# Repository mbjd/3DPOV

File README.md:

# 3DPOV

This is the github repo for my 3D persistence of vision display. Here you
can find the arduino/teensy source code (`./code/`), eagle schematic and
board files (`./Eagle/`), and the python program I wrote to simplify the
creation of images containing simple shapes (`./image_creation/`).

### Videos

[one](https://www.youtube.com/watch?v=bCETWNgBxbI) [two](https://www.youtube.com/watch?v=-gFsKhf5J-I)

### Summary

This was my Matura project (the end of (the equivalent of) high school in
Switzerland), and I did most of the work in the second half of 2014. You
can find various more detailed reports below, but here's a quick summary:

The *very* basic idea is this: We have a 2D display
and rotate it quickly through the third dimension. By controlling each 
pixel in a precisely timed way, we can light up a set of points in 3D 
space, but only at specific times (when the corresponding pixel is
physically at the right spot). When this rotation is fast enough, 
[persistence of vision](https://en.wikipedia.org/wiki/Persistence_of_vision) 
will make it seem like an actual 3D image is continuously displayed. 

The display itself consists of 10 LED rows mounted in a double-helix
arrangement. Each of them contains 16 RGB LEDs driven by three shift
registers, for a total of 480 LEDs or 160 Pixels.

The shift registers are controlled by a Teensy 3.1 microcontroller board
using an SPI bus (All 30 shift registers are daisy chained together). The
controller is mounted on a wooden disc below the ten LED boards.

All of this is mounted on a 4mm steel shaft, supplied with 3.3V DC using
two copper slip rings, and spun up to 60 Hz by a brushed DC motor. A hall
sensor and a magnet enable the controller to measure the rotational speed
and to adjust its timing, so that the image always stays still despite the
speed not being quite constant. The image is updated 100 times per
revolution, or 6000 times a second.

Currently there's no way to supply images at runtime, the display has to be
stopped so that a new program can be uploaded using the Teensy's USB port.

### Various versions of the paper

[Original in German](https://drive.google.com/file/d/0B2iq6C3wqe05aEx5dVFoNF9xR28/view?usp=sharing&resourcekey=0-dw7vPy6Eh3UUGyYrgM35uw)

[English long version, not quite finished](https://github.com/mbjd/english-paper/blob/master/paper.pdf)

[English short version](https://github.com/mbjd/english-paper/blob/master/paper-short.pdf)

[Other english stuff](https://github.com/mbjd/english-paper)

### Press etc

[Hackaday article](http://hackaday.com/2016/11/16/spinning-3d-pov-display-as-a-high-school-term-project/)

[ETHZ D-ITET in German](https://www.ee.ethz.ch/de/news-und-veranstaltungen/d-itet-news-channel/2016/09/d-itet-student-gewinnt-forschungs-preis-.html) or [English](https://www.ee.ethz.ch/news-and-events/d-itet-news-channel/2016/09/d-itet-student-wins-research-award.html)

[Swiss Youth in Science article](http://web.archive.org/web/20161117130814/http://sjf.ch/eucys-2016-eth-student-gewinnt-forschungs-preis-am-ersten-studientag/)

[EUCYS 2016 link](http://eucys2016.eu/development-of-a-3d-display/)

### Links to discussion

[one](http://www.reddit.com/r/electronics/comments/2m6apx/finally_my_led_board_works_had_to_make_a_little/) [two](http://www.reddit.com/r/electronics/comments/2nrek4/almost_working_3d_pov_display/) [three](http://www.reddit.com/r/electronics/comments/2q9sg6/my_3d_pov_in_action_as_promised/)

### Photos

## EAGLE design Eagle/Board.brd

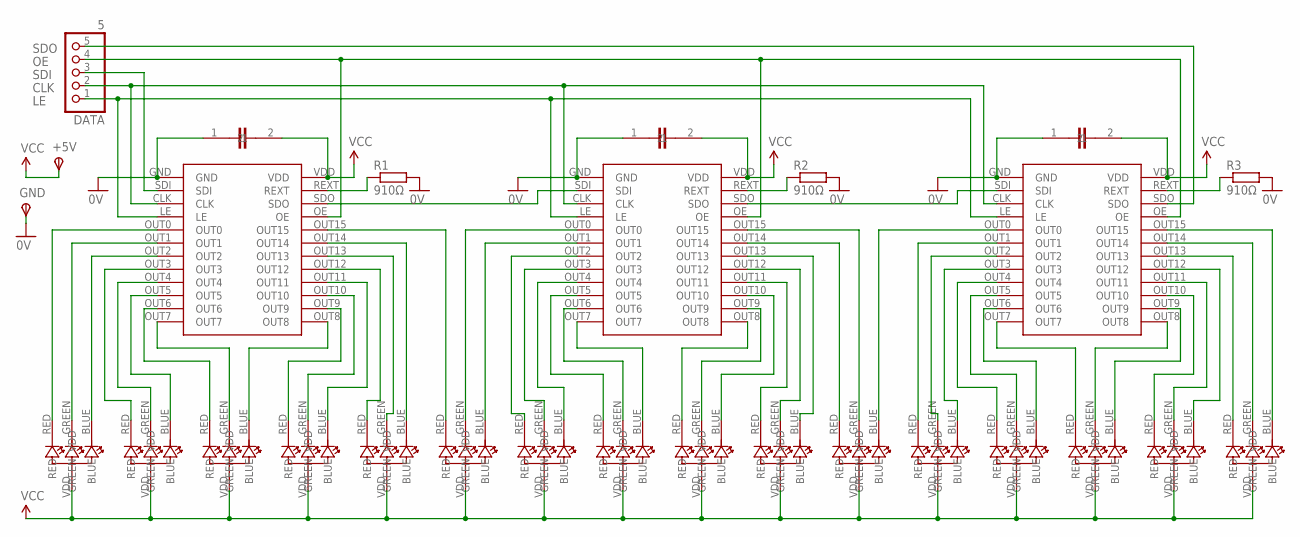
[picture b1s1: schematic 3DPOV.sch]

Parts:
+5V: TPSPAD1-20; P1-20
CAP1, CAP2, CAP3: 1µF; CAP
DATA: 5; 1X05
GND: TPSPAD1-20; P1-20
IC1, IC2, IC3: TLC5927; DBQ
R1, R2, R3: 910Ω; 0207/7
U$1, U$2, U$4, U$5, U$6, U$7, U$10, U$11, U$12, U$13, U$14, U$15, U$16, U$17, U$18, U$19: SMDLED

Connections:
0V: CAP1.1, CAP2.1, CAP3.1, GND.TP, IC1.GND, IC2.GND, IC3.GND, R1.2, R2.2, R3.2
CLK: DATA.2, IC1.CLK, IC2.CLK, IC3.CLK
LE: DATA.1, IC1.LE, IC2.LE, IC3.LE
unnamed: IC1.OUT0, U$4.RED
unnamed: IC1.OUT1, U$4.GREEN
unnamed: IC1.OUT2, U$4.BLUE
unnamed: IC1.OUT3, U$5.RED
unnamed: IC1.OUT4, U$5.GREEN
unnamed: IC1.OUT5, U$5.BLUE
unnamed: IC1.OUT7, U$6.GREEN
unnamed: IC1.OUT6, U$6.RED
unnamed: IC1.OUT8, U$6.BLUE
unnamed: IC1.OUT9, U$7.RED
unnamed: IC1.OUT10, U$7.GREEN
unnamed: IC1.OUT11, U$7.BLUE
unnamed: IC1.OUT12, U$2.RED
unnamed: IC1.OUT13, U$2.GREEN
unnamed: IC1.OUT14, U$2.BLUE
unnamed: IC1.OUT15, U$1.RED
unnamed: IC2.OUT0, U$1.GREEN
unnamed: IC2.OUT1, U$1.BLUE
unnamed: IC2.OUT2, U$10.RED
unnamed: IC2.OUT3, U$10.GREEN
unnamed: IC2.OUT4, U$10.BLUE
unnamed: IC2.OUT7, U$11.BLUE
unnamed: IC2.OUT6, U$11.GREEN
unnamed: IC2.OUT5, U$11.RED
unnamed: IC2.OUT11, U$13.RED
unnamed: IC2.OUT12, U$13.GREEN
unnamed: IC2.OUT13, U$13.BLUE
unnamed: IC2.OUT14, U$14.RED
unnamed: IC2.OUT15, U$14.GREEN
unnamed: IC3.OUT0, U$14.BLUE
unnamed: IC3.OUT1, U$15.RED
unnamed: IC3.OUT2, U$15.GREEN
unnamed: IC3.OUT3, U$15.BLUE
unnamed: IC3.OUT4, U$16.RED
unnamed: IC3.OUT5, U$16.GREEN
unnamed: IC3.OUT7, U$17.RED
unnamed: IC3.OUT6, U$16.BLUE
unnamed: IC3.OUT8, U$17.GREEN
unnamed: IC3.OUT9, U$17.BLUE
unnamed: IC3.OUT10, U$18.RED
unnamed: IC3.OUT11, U$18.GREEN
unnamed: IC3.OUT12, U$18.BLUE
unnamed: IC3.OUT13, U$19.RED
unnamed: IC3.OUT14, U$19.GREEN
unnamed: IC3.OUT15, U$19.BLUE
unnamed: IC3.REXT, R3.1
unnamed: IC1.SDO, IC2.SDI
unnamed: IC2.SDO, IC3.SDI
unnamed: IC2.REXT, R2.1
unnamed: IC1.REXT, R1.1
unnamed: IC2.OUT8, U$12.RED
unnamed: IC2.OUT9, U$12.GREEN
unnamed: IC2.OUT10, U$12.BLUE
OE: DATA.4, IC1.OE, IC2.OE, IC3.OE
SDI: DATA.3, IC1.SDI
SDO: DATA.5, IC3.SDO
VCC: +5V.TP, CAP1.2, CAP2.2, CAP3.2, IC1.VDD, IC2.VDD, IC3.VDD, U$1.VDD, U$2.VDD, U$4.VDD, U$5.VDD, U$6.VDD, U$7.VDD, U$10.VDD, U$11.VDD, U$12.VDD, U$13.VDD, U$14.VDD, U$15.VDD, U$16.VDD, U$17.VDD, U$18.VDD, U$19.VDD

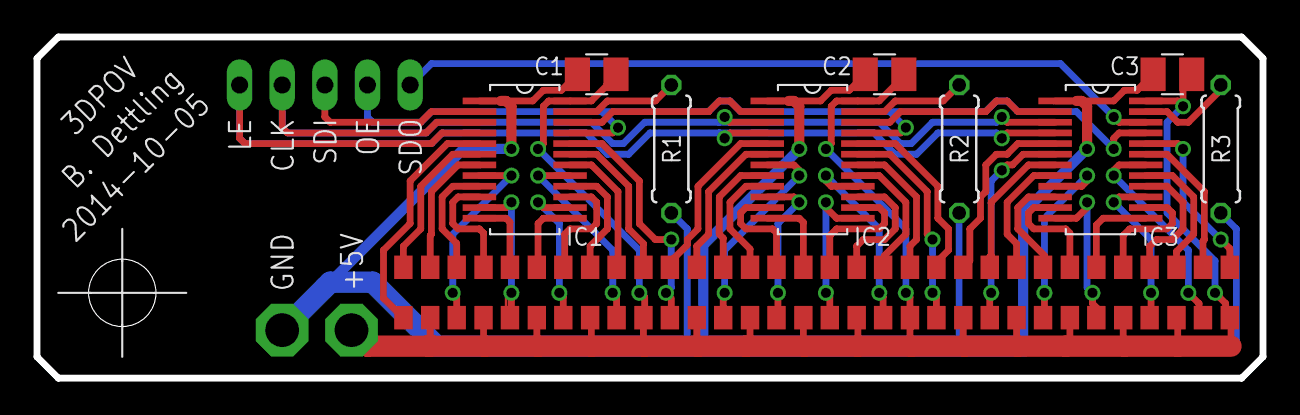
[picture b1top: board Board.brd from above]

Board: 2 copper layers, 73.0 x 20.3 mm, 28 parts (0 on the bottom side), 60 nets.

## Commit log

2014-12-16 First commit
    Arduino sketch that runs on a teensy 3.1 and updates the display’s LEDs
    via their SPI drivers. Rotation sync using a hall sensor.
2014-12-16 Created README.md
2014-12-17 Added Animated in its own folder so that the Arduino IDE doesn't go crazy
2014-12-17 made an image of a turning line
2014-12-17 Added a period/300 delay after each refresh to separate pixels
2014-12-17 Made a green smiley face on the bottom layer
2014-12-24 Added Eagle -sch and .brd files
2014-12-24 Added pixel layout files & Matura paper
2014-12-24 Renamed some files for clarity
2014-12-25 experimented around with timing (micros() vs elapsedMicros) Please enter the commit message for your changes. Lines starting
2014-12-29 Added floating average period meaurements for less jitter
2015-01-10 Improved image stabilisation
2015-01-13 Added reddit links to README
2015-01-28 Added very thorough comments
2015-01-31 Added program that displays current frequency and period
2015-01-31 Un-averaged values are displayed, but averages are used to smooth the image out
2015-02-01 Speedmeter can now display any string from ASCII 32 to 126
2015-02-18 Polished comments and formatting
2015-02-27 Included images
2015-02-27 Images are now directly linked to
2015-02-27 Also linked to PDF
2015-03-07 correction about rightshift and division
2015-05-04 Added video link
2015-07-12 wording
2015-07-12 Wording etc.
2015-12-27 Minor rewording
2015-12-27 Started RC receiver interface
2015-12-27 Deleted temporary file
2016-03-07 Added python program to create images
2016-03-07 Fixed typo
2016-03-07 Refreshed empty image program
2016-03-07 New speedmeter, removed animated
2016-03-07 Better folder structure
2016-03-07 Some documentation, cleaned up
2016-03-07 Moved sketches for arduino IDE
2016-03-07 Documentation for drawCuboid
2016-03-07 Can now plot functions
2016-03-10 Faster point distance function, sphere is now implemented without line, plot function with bool as result
2016-03-10 Redefined functions in terms of plotBoolFunction, added hollow sphere function
2016-03-10 Restructured, separated code blocks
2016-03-13 Better comments, check for equal value instead of identity
2016-04-21 minor formatting issue
2016-05-14 Added link to english paper
2016-05-14 Added another \n
2016-05-25 clearer variable names
2016-08-20 reworked links in README
2016-10-05 minor changes
    removed leading _ completely
    mv Sketches/ code
2016-10-20 gotta be honest here
2016-11-27 included some links to articles
2016-12-20 EUCYS for the win
2017-01-06 More information in README.md
2017-01-06 moved images to repo
2017-01-14 more structure in readme
2017-02-07 typo
2018-03-24 fixed dead link

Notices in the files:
parts and their libraries:
SparkFun-Aesthetics: Licensing: Creative Commons ShareAlike 4.0 International - https://creativecommons.org/licenses/by-sa/4.0
